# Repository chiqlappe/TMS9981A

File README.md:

# TMS9981Aビデオカード

## 概要
* PC-8001などからTMS9981Aを制御してビデオ出力を行うための拡張基板

## 使用環境
* PC-8001+PC-8012
* PC-8001mk2/SR
* PC-8801シリーズ（未確認）

## I/Oポート
|I/O|アドレス|用途|
|:--|:--|:--|
|IN/OUT|$98|データポート|
|IN/OUT|$99|コントロールポート|

## 参考サイト
[KUNINET BLOGさん](https://kuninet.org/2019/11/23/kz80%e3%83%9e%e3%82%a4%e3%82%b3%e3%83%b3-%e5%81%bdmsx1%e3%81%b8%e3%80%9c%e3%83%93%e3%83%87%e3%82%aa%e3%83%9c%e3%83%bc%e3%83%891/)

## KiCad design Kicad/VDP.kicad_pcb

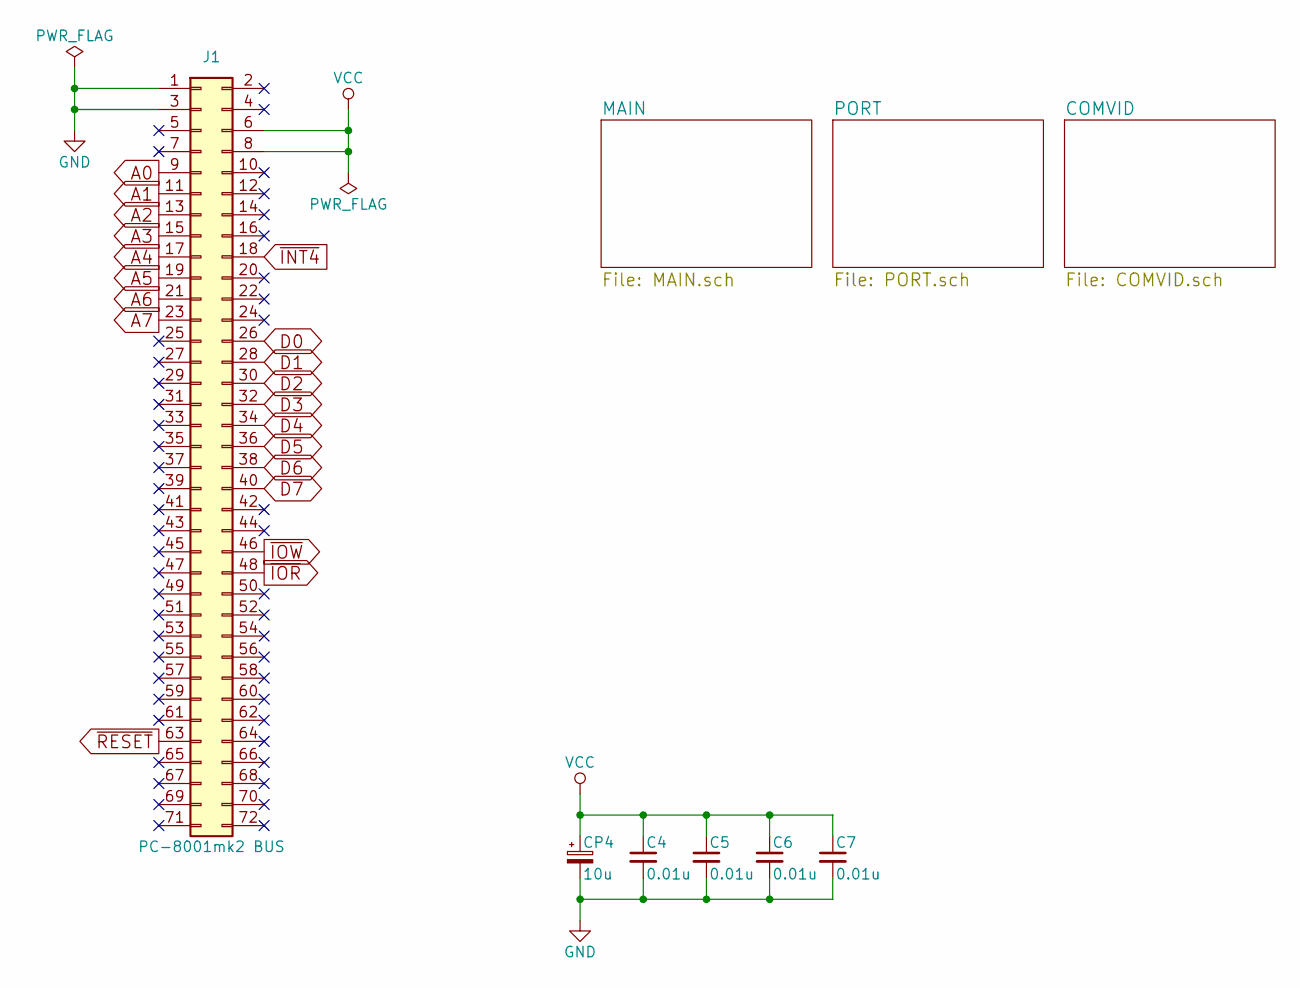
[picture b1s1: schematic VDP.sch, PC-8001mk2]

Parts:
C4, C5, C6, C7: 0.01u; C_Disc_D3.0mm_W1.6mm_P2.50mm
CP4: 10u; CP_Radial_D5.0mm_P2.50mm
J1: PC-8001mk2 BUS; PC88_72_ODD_EVEN

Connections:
A0: J1.9; also elsewhere on the board
A1: J1.11; also elsewhere on the board
A2: J1.13; also elsewhere on the board
A3: J1.15; also elsewhere on the board
A4: J1.17; also elsewhere on the board
A5: J1.19; also elsewhere on the board
A6: J1.21; also elsewhere on the board
A7: J1.23; also elsewhere on the board
D0: J1.26; also elsewhere on the board
D1: J1.28; also elsewhere on the board
D2: J1.30; also elsewhere on the board
D3: J1.32; also elsewhere on the board
D4: J1.34; also elsewhere on the board
D5: J1.36; also elsewhere on the board
D6: J1.38; also elsewhere on the board
D7: J1.40; also elsewhere on the board
GND: C4.2, C5.2, C6.2, C7.2, CP4.2, J1.1, J1.3; also elsewhere on the board
VCC: C4.1, C5.1, C6.1, C7.1, CP4.1, J1.6, J1.8; also elsewhere on the board
~INT4: J1.18; also elsewhere on the board
~IOR: J1.48; also elsewhere on the board
~IOW: J1.46; also elsewhere on the board
~RESET: J1.63; also elsewhere on the board

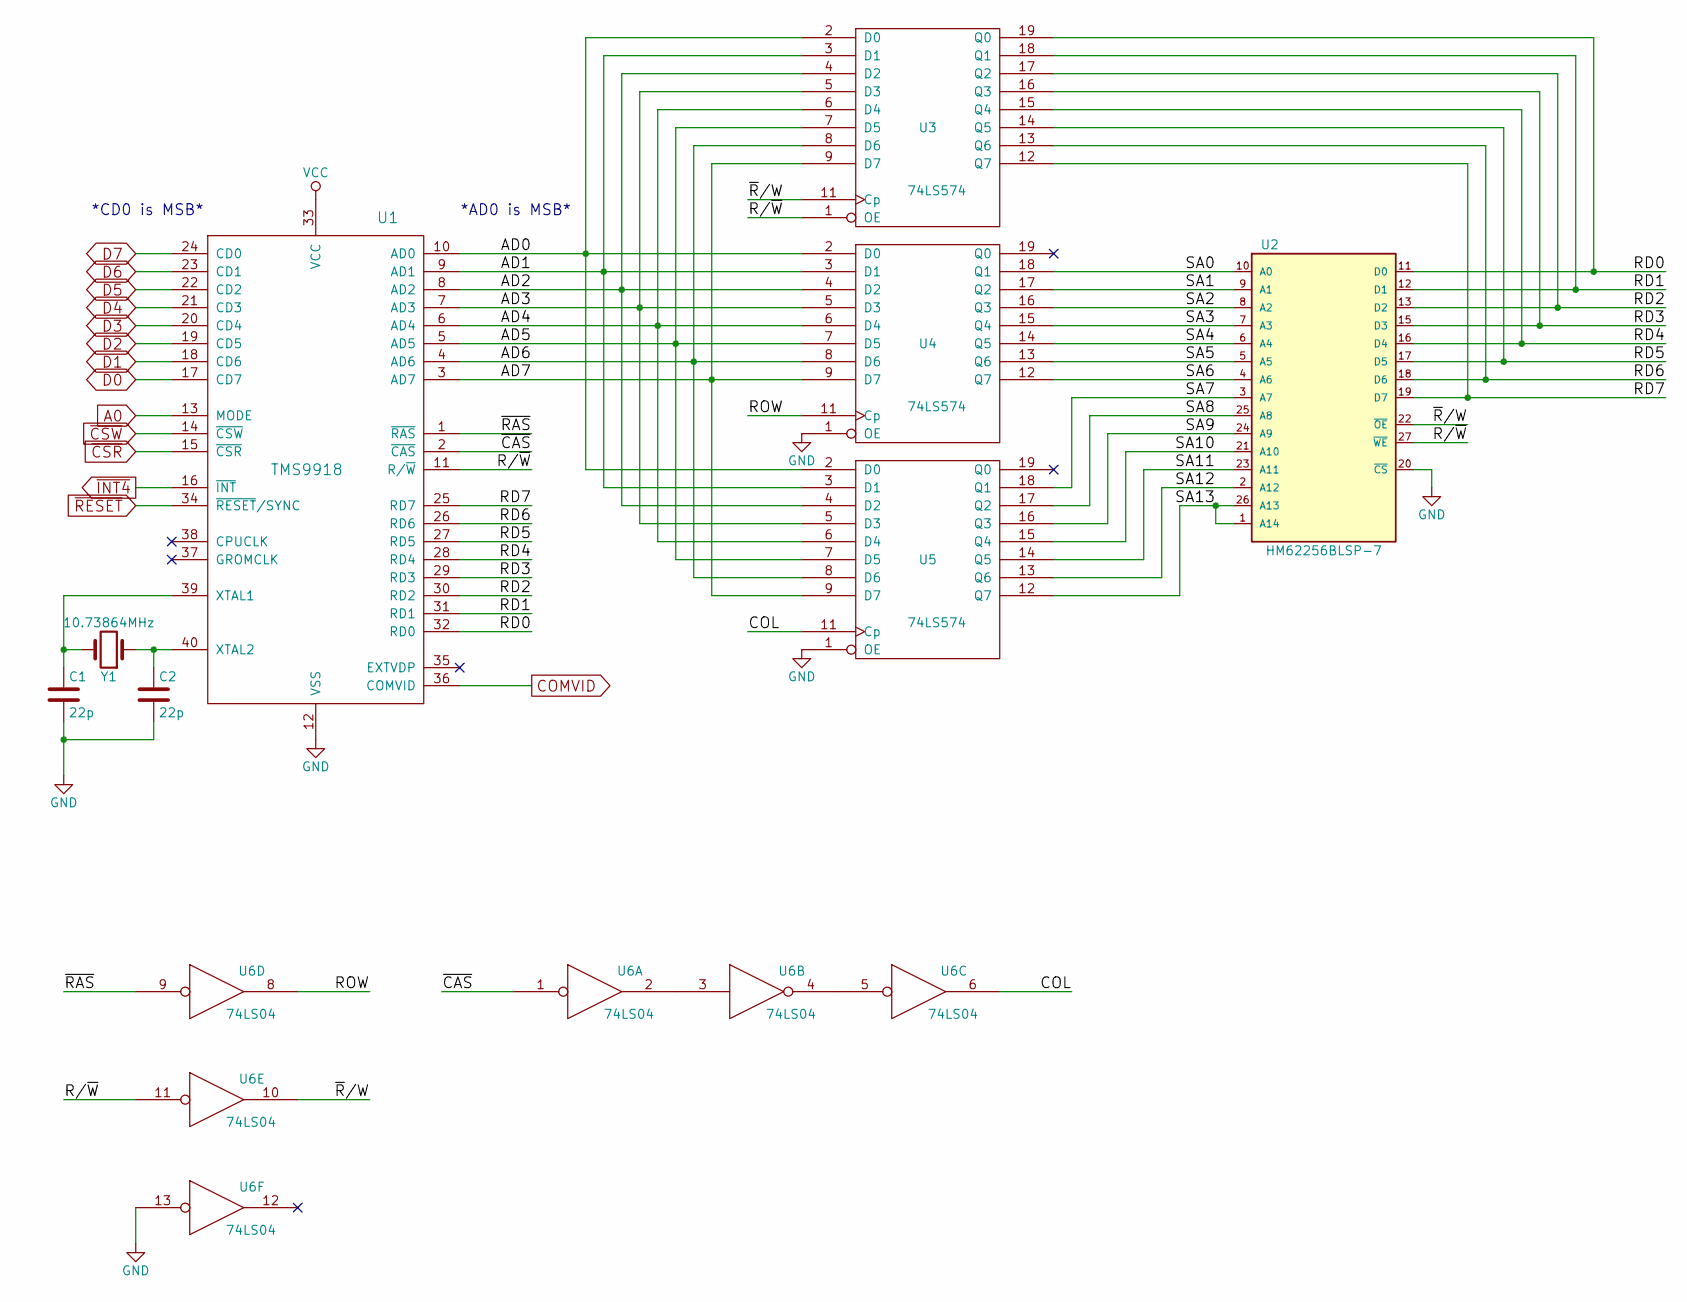
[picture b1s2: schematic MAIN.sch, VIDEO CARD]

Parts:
C1, C2: 22p; C_Disc_D3.0mm_W1.6mm_P2.50mm
U1: TMS9918; DIP-40_W15.24mm_Socket
U2: HM62256BLSP-7; DIP-28_W15.24mm_Socket
U3, U4, U5: 74LS574; DIP-20_W7.62mm_Socket
U6: 74LS04; DIP-14_W7.62mm_Socket
Y1: 10.73864MHz; Crystal_HC49-4H_Vertical

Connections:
/MAIN/AD0: U1.10 (AD0), U3.2 (D0), U4.2 (D0), U5.2 (D0)
/MAIN/AD1: U1.9 (AD1), U3.3 (D1), U4.3 (D1), U5.3 (D1)
/MAIN/AD2: U1.8 (AD2), U3.4 (D2), U4.4 (D2), U5.4 (D2)
/MAIN/AD3: U1.7 (AD3), U3.5 (D3), U4.5 (D3), U5.5 (D3)
/MAIN/AD4: U1.6 (AD4), U3.6 (D4), U4.6 (D4), U5.6 (D4)
/MAIN/AD5: U1.5 (AD5), U3.7 (D5), U4.7 (D5), U5.7 (D5)
/MAIN/AD6: U1.4 (AD6), U3.8 (D6), U4.8 (D6), U5.8 (D6)
/MAIN/AD7: U1.3 (AD7), U3.9 (D7), U4.9 (D7), U5.9 (D7)
/MAIN/COL: U5.11 (Cp), U6.6
/MAIN/R/~W: U1.11 (R/~W), U2.27 (~WE), U3.1 (OE), U6.11
/MAIN/RD0: U1.32 (RD0), U2.11 (D0), U3.19 (Q0)
/MAIN/RD1: U1.31 (RD1), U2.12 (D1), U3.18 (Q1)
/MAIN/RD2: U1.30 (RD2), U2.13 (D2), U3.17 (Q2)
/MAIN/RD3: U1.29 (RD3), U2.15 (D3), U3.16 (Q3)
/MAIN/RD4: U1.28 (RD4), U2.16 (D4), U3.15 (Q4)
/MAIN/RD5: U1.27 (RD5), U2.17 (D5), U3.14 (Q5)
/MAIN/RD6: U1.26 (RD6), U2.18 (D6), U3.13 (Q6)
/MAIN/RD7: U1.25 (RD7), U2.19 (D7), U3.12 (Q7)
/MAIN/ROW: U4.11 (Cp), U6.8
/MAIN/SA0: U2.10 (A0), U4.18 (Q1)
/MAIN/SA1: U2.9 (A1), U4.17 (Q2)
/MAIN/SA2: U2.8 (A2), U4.16 (Q3)
/MAIN/SA3: U2.7 (A3), U4.15 (Q4)
/MAIN/SA4: U2.6 (A4), U4.14 (Q5)
/MAIN/SA5: U2.5 (A5), U4.13 (Q6)
/MAIN/SA6: U2.4 (A6), U4.12 (Q7)
/MAIN/SA7: U2.3 (A7), U5.18 (Q1)
/MAIN/SA8: U2.25 (A8), U5.17 (Q2)
/MAIN/SA9: U2.24 (A9), U5.16 (Q3)
/MAIN/SA10: U2.21 (A10), U5.15 (Q4)
/MAIN/SA11: U2.23 (A11), U5.14 (Q5)
/MAIN/SA12: U2.2 (A12), U5.13 (Q6)
/MAIN/SA13: U2.1 (A14), U2.26 (A13), U5.12 (Q7)
/MAIN/~CAS: U1.2 (~CAS), U6.1
/MAIN/~RAS: U1.1 (~RAS), U6.9
/MAIN/~R~/W: U2.22 (~OE), U3.11 (Cp), U6.10
A0: U1.13 (MODE); also elsewhere on the board
COMVID: U1.36 (COMVID); also elsewhere on the board
D0: U1.17 (CD7); also elsewhere on the board
D1: U1.18 (CD6); also elsewhere on the board
D2: U1.19 (CD5); also elsewhere on the board
D3: U1.20 (CD4); also elsewhere on the board
D4: U1.21 (CD3); also elsewhere on the board
D5: U1.22 (CD2); also elsewhere on the board
D6: U1.23 (CD1); also elsewhere on the board
D7: U1.24 (CD0); also elsewhere on the board
GND: C1.2, C2.2, U1.12 (VSS), U2.14 (GND), U2.20 (~CS), U3.10 (GND), U4.1 (OE), U4.10 (GND), U5.1 (OE), U5.10 (GND), U6.7 (GND), U6.13; also elsewhere on the board
unnamed: C1.1, U1.39 (XTAL1), Y1.2
unnamed: C2.1, U1.40 (XTAL2), Y1.1
unnamed: U6.2, U6.3
unnamed: U6.4, U6.5
VCC: U1.33 (VCC), U2.28 (VCC), U3.20 (VCC), U4.20 (VCC), U5.20 (VCC), U6.14 (VCC); also elsewhere on the board
~CSR: U1.15 (~CSR); also elsewhere on the board
~CSW: U1.14 (~CSW); also elsewhere on the board
~INT4: U1.16 (~INT); also elsewhere on the board
~RESET: U1.34 (~RESET~/SYNC); also elsewhere on the board

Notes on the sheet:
*AD0 is MSB*
*CD0 is MSB*

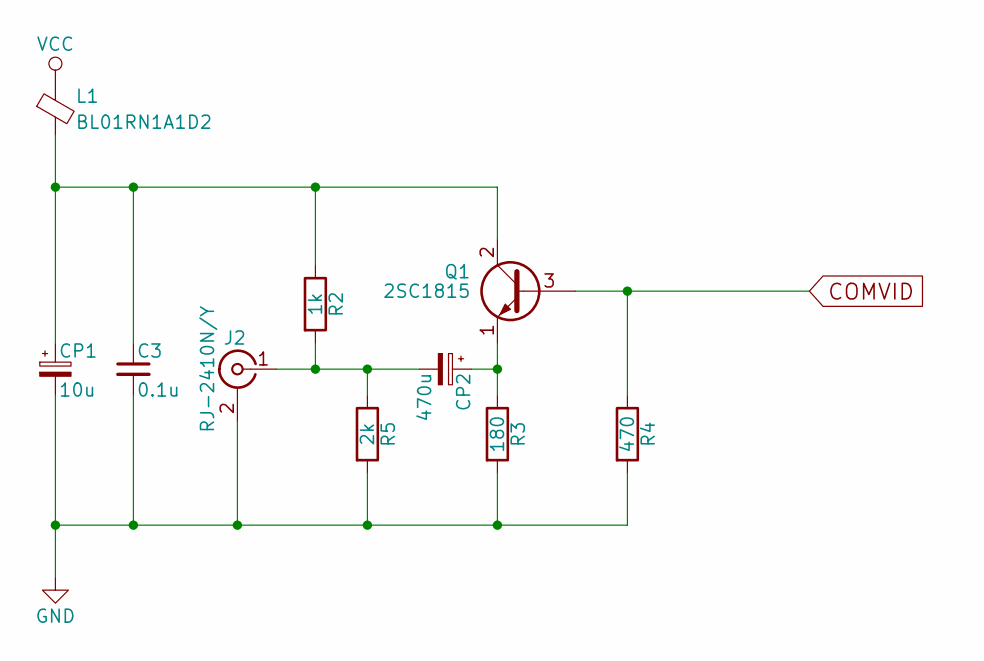
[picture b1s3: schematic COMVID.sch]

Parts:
C3: 0.1u; C_Disc_D3.0mm_W1.6mm_P2.50mm
CP1: 10u; CP_Radial_D5.0mm_P2.50mm
CP2: 470u; CP_Radial_D6.3mm_P2.50mm
J2: RJ-2410N/Y; RJ-2410N
L1: BL01RN1A1D2; R_Axial_DIN0204_L3.6mm_D1.6mm_P7.62mm_Horizontal
Q1: 2SC1815; TO-92_Inline_Wide
R2: 1k; R_Axial_DIN0204_L3.6mm_D1.6mm_P7.62mm_Horizontal
R3: 180; R_Axial_DIN0204_L3.6mm_D1.6mm_P7.62mm_Horizontal
R4: 470; R_Axial_DIN0204_L3.6mm_D1.6mm_P7.62mm_Horizontal
R5: 2k; R_Axial_DIN0204_L3.6mm_D1.6mm_P7.62mm_Horizontal

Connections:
COMVID: Q1.3 (B), R4.1; also elsewhere on the board
GND: C3.2, CP1.2, J2.2 (Ext), R3.2, R4.2, R5.2; also elsewhere on the board
unnamed: C3.1, CP1.1, L1.2, Q1.2 (C), R2.1
unnamed: CP2.1, Q1.1 (E), R3.1
unnamed: CP2.2, J2.1 (In), R2.2, R5.1
VCC: L1.1; also elsewhere on the board

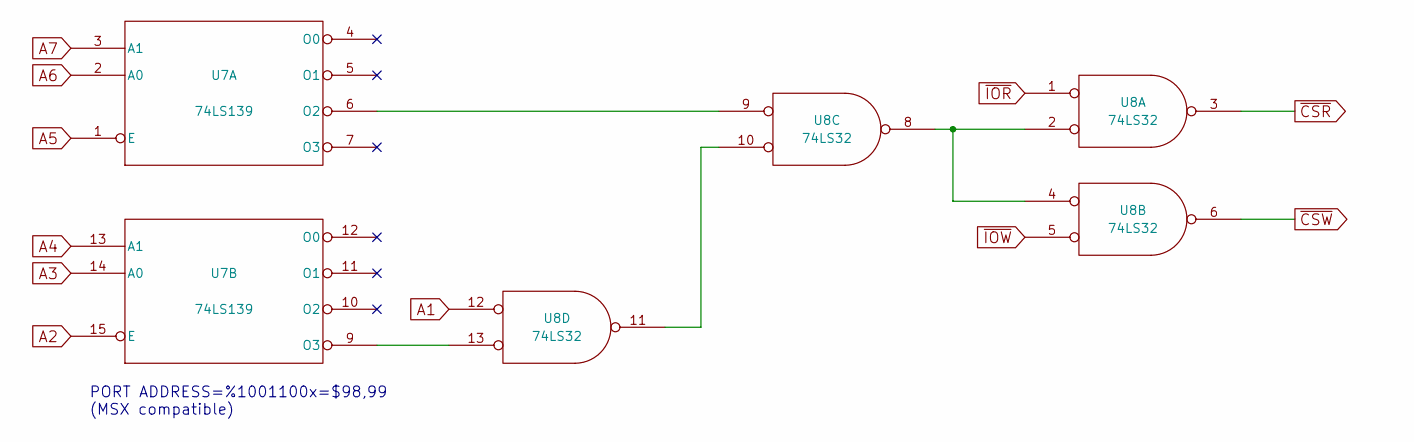
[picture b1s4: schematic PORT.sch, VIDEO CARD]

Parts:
U7: 74LS139; DIP-16_W7.62mm_Socket
U8: 74LS32; DIP-14_W7.62mm_Socket

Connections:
A1: U8.12; also elsewhere on the board
A2: U7.15 (E); also elsewhere on the board
A3: U7.14 (A0); also elsewhere on the board
A4: U7.13 (A1); also elsewhere on the board
A5: U7.1 (E); also elsewhere on the board
A6: U7.2 (A0); also elsewhere on the board
A7: U7.3 (A1); also elsewhere on the board
GND: U7.8 (GND), U8.7 (GND); also elsewhere on the board
unnamed: U7.6 (O2), U8.9
unnamed: U7.9 (O3), U8.13
unnamed: U8.2, U8.4, U8.8
unnamed: U8.10, U8.11
VCC: U7.16 (VCC), U8.14 (VCC); also elsewhere on the board
~CSR: U8.3; also elsewhere on the board
~CSW: U8.6; also elsewhere on the board
~IOR: U8.1; also elsewhere on the board
~IOW: U8.5; also elsewhere on the board

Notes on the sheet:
PORT ADDRESS=%1001100x=$98,99 (MSX compatible)

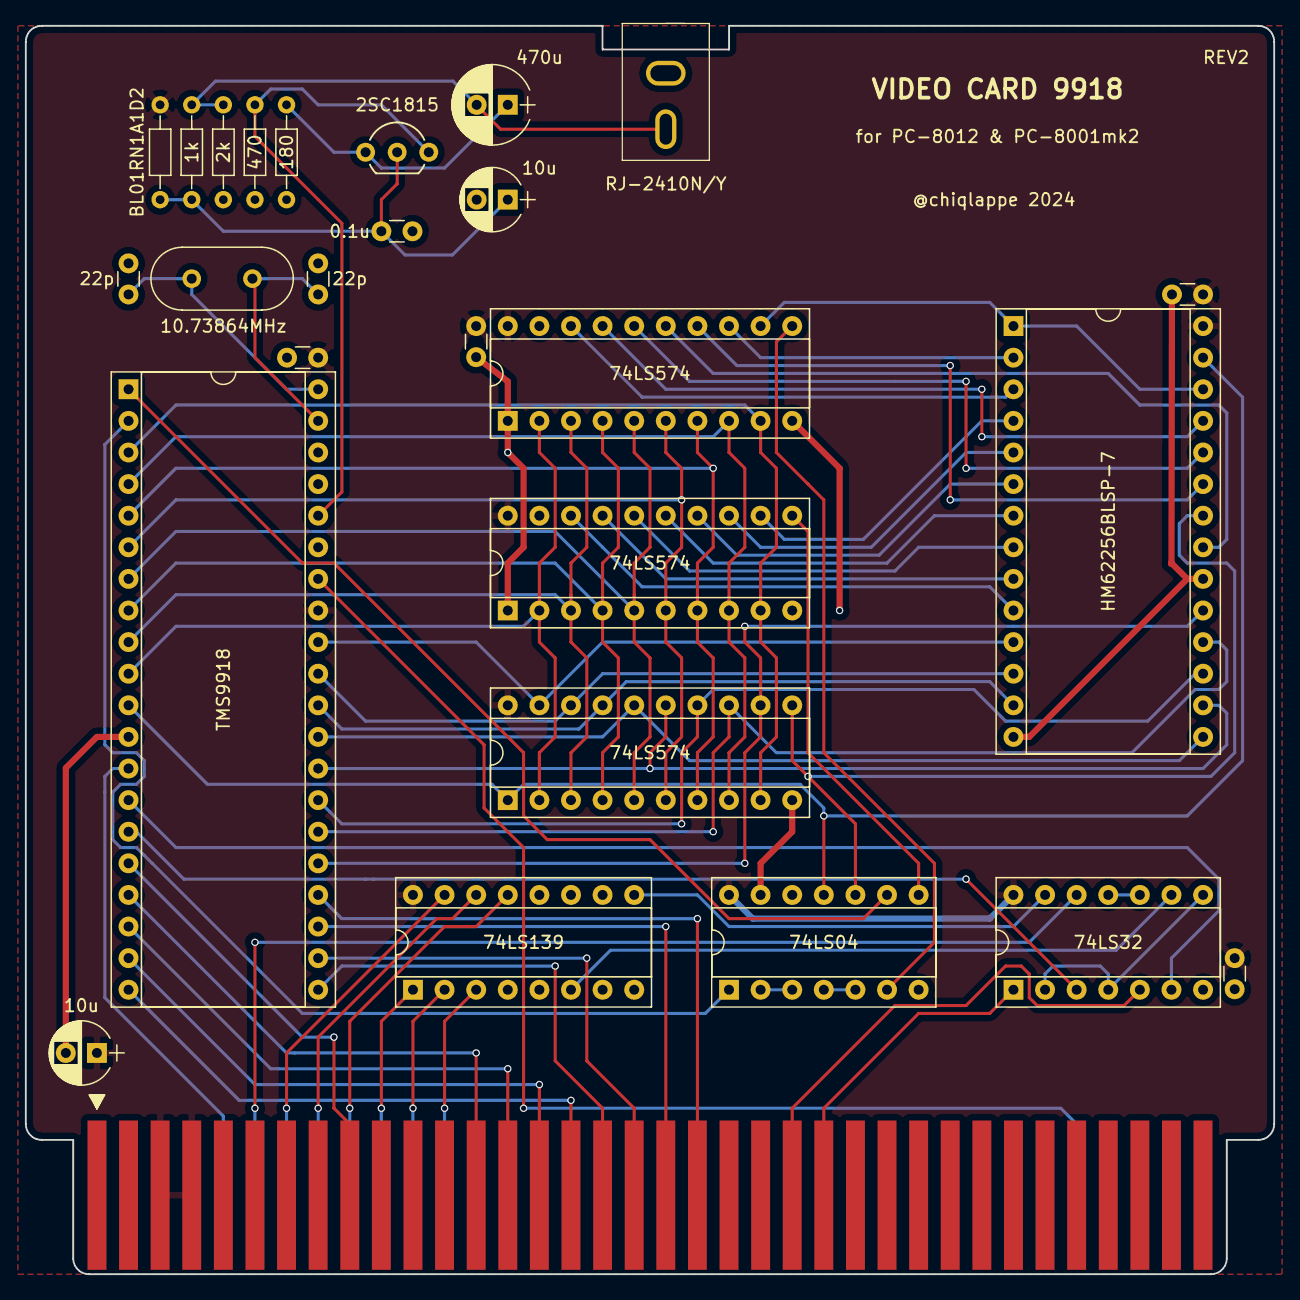
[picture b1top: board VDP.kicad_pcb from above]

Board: 2 copper layers, 100.3 x 100.3 mm, 27 parts (0 on the bottom side), 72 nets.
